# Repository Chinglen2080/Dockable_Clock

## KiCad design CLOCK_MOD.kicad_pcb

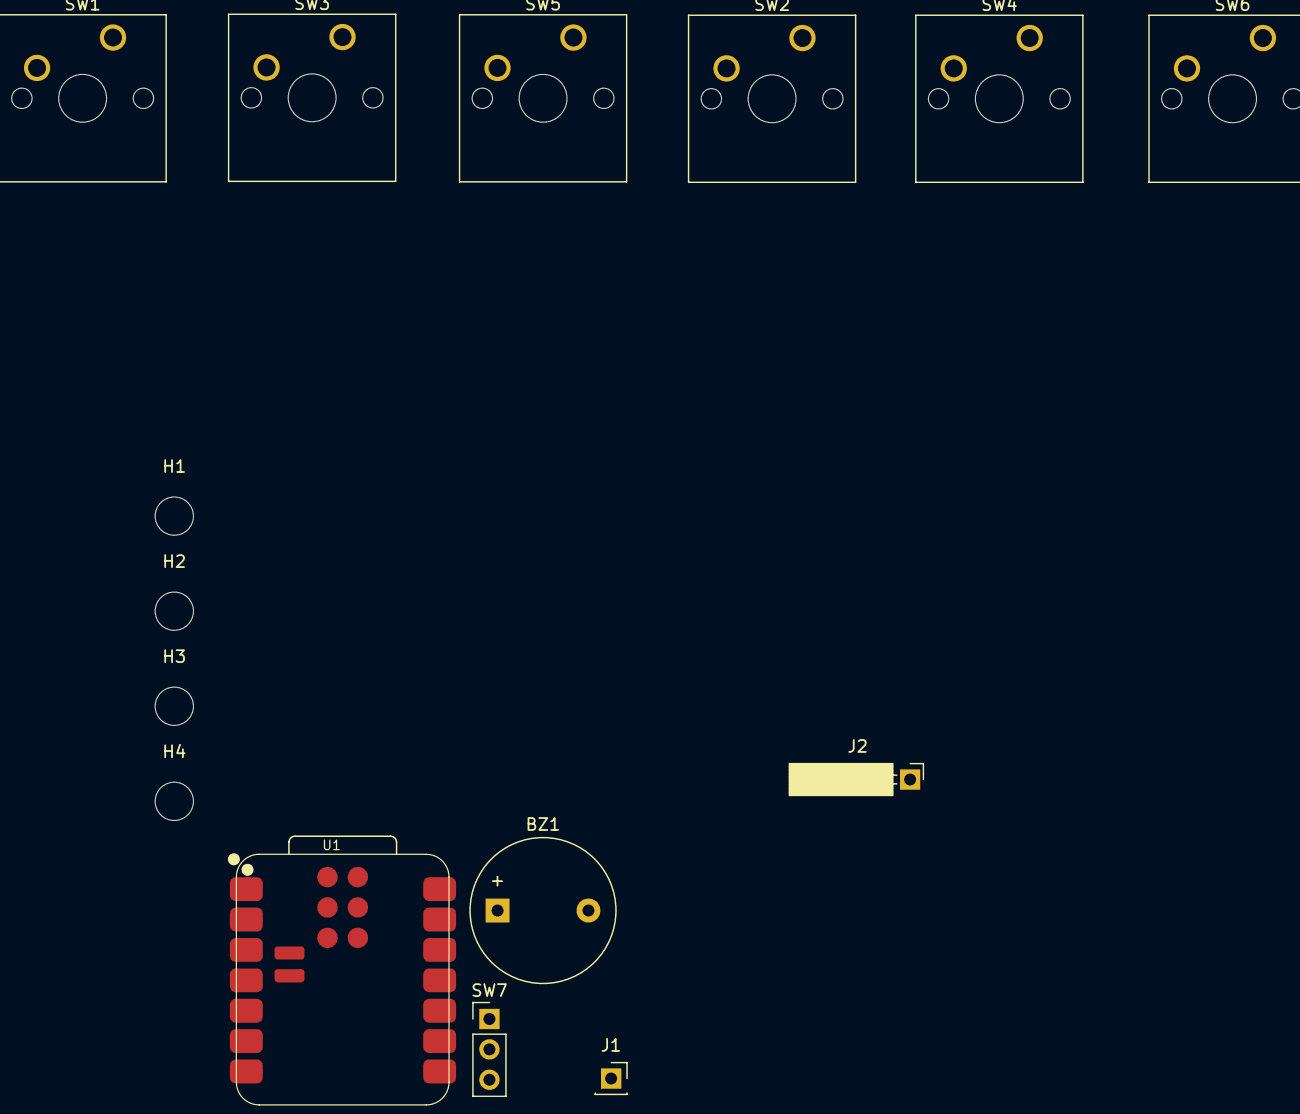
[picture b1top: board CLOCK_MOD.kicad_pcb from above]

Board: 2 copper layers, 15 parts (0 on the bottom side), 10 nets, no tracks yet.

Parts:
BZ1: Buzzer; Buzzer_12x9.5RM7.6
H1, H2, H3, H4: MountingHole; MountingHole_3.2mm_M3
J1: Conn_01x08_Pin; PinSocket_1x01_P2.54mm_Vertical
J2: Conn_01x10_Pin; PinSocket_1x01_P2.54mm_Horizontal
SW1, SW2, SW3, SW4, SW5, SW6: SW_Push; SW_Cherry_MX_1.00u_PCB
SW7: SW_SPST; PinHeader_1x03_P2.54mm_Vertical
U1: XIAO-ESP32-C3-SMD

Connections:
GND: BZ1.2 (-), J1.1 (Pin_1_1), SW1.1, SW2.1, SW3.1, SW4.1, SW5.1, SW6.1, U1.13 (GND), U1.18 (GND), U1.22 (GND)
unnamed: BZ1.1 (+), SW7.2 (B)
unnamed: J2.1 (Pin_1_1), U1.10 (D9/BOOT)
unnamed: SW2.2, U1.2 (D1)
unnamed: SW3.2, U1.3 (D2)
unnamed: SW4.2, U1.4 (D3)
unnamed: SW5.2, U1.7 (D6)
unnamed: SW6.2, U1.9 (D8)
unnamed: SW7.1 (A), U1.8 (D7)
unnamed: SW1.2, U1.1 (D0)
